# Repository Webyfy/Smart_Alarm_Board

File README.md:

View this project on [CADLAB.io](https://cadlab.io/project/27515). 

# Smart_Alarm_Board

## Description
Let people know what your project can do specifically. Provide context and add a link to any reference visitors might be unfamiliar with. A list of Features or a Background subsection can also be added here. If there are alternatives to your project, this is a good place to list differentiating factors.

## Badges
On some READMEs, you may see small images that convey metadata, such as whether or not all the tests are passing for the project. You can use Shields to add some to your README. Many services also have instructions for adding a badge.

## Visuals
Depending on what you are making, it can be a good idea to include screenshots or even a video (you'll frequently see GIFs rather than actual videos). Tools like ttygif can help, but check out Asciinema for a more sophisticated method.

## Installation
Within a particular ecosystem, there may be a common way of installing things, such as using Yarn, NuGet, or Homebrew. However, consider the possibility that whoever is reading your README is a novice and would like more guidance. Listing specific steps helps remove ambiguity and gets people to using your project as quickly as possible. If it only runs in a specific context like a particular programming language version or operating system or has dependencies that have to be installed manually, also add a Requirements subsection.

## Usage
Use examples liberally, and show the expected output if you can. It's helpful to have inline the smallest example of usage that you can demonstrate, while providing links to more sophisticated examples if they are too long to reasonably include in the README.

## Support
Tell people where they can go to for help. It can be any combination of an issue tracker, a chat room, an email address, etc.

## Roadmap
If you have ideas for releases in the future, it is a good idea to list them in the README.

## Contributing
State if you are open to contributions and what your requirements are for accepting them.

For people who want to make changes to your project, it's helpful to have some documentation on how to get started. Perhaps there is a script that they should run or some environment variables that they need to set. Make these steps explicit. These instructions could also be useful to your future self.

You can also document commands to lint the code or run tests. These steps help to ensure high code quality and reduce the likelihood that the changes inadvertently break something. Having instructions for running tests is especially helpful if it requires external setup, such as starting a Selenium server for testing in a browser.

## Authors and acknowledgment
Show your appreciation to those who have contributed to the project.

## License
For open source projects, say how it is licensed.

## Project status
If you have run out of energy or time for your project, put a note at the top of the README saying that development has slowed down or stopped completely. Someone may choose to fork your project or volunteer to step in as a maintainer or owner, allowing your project to keep going. You can also make an explicit request for maintainers.

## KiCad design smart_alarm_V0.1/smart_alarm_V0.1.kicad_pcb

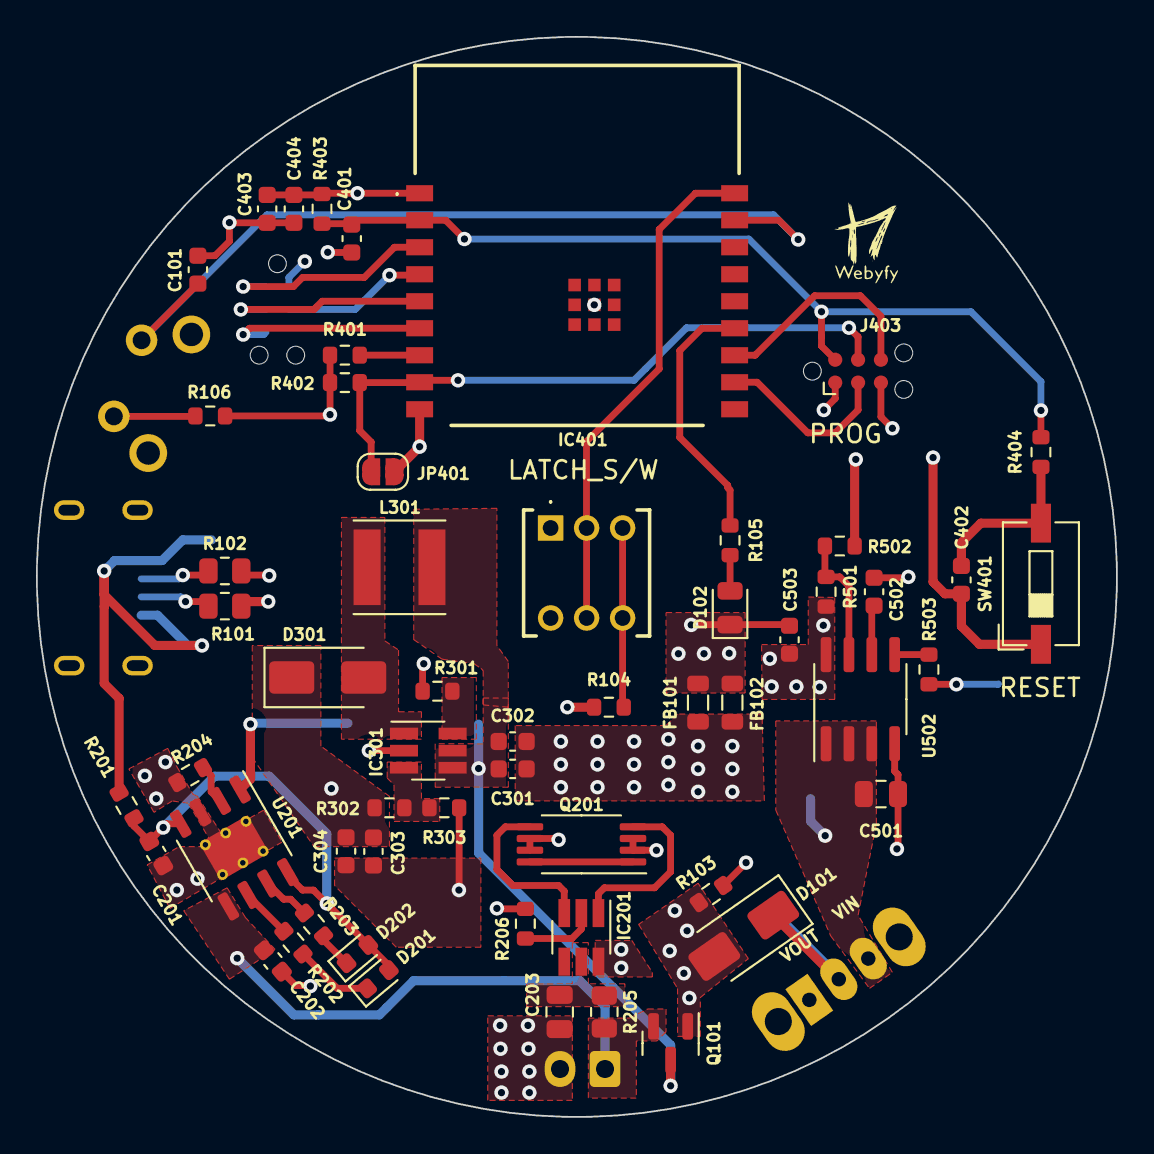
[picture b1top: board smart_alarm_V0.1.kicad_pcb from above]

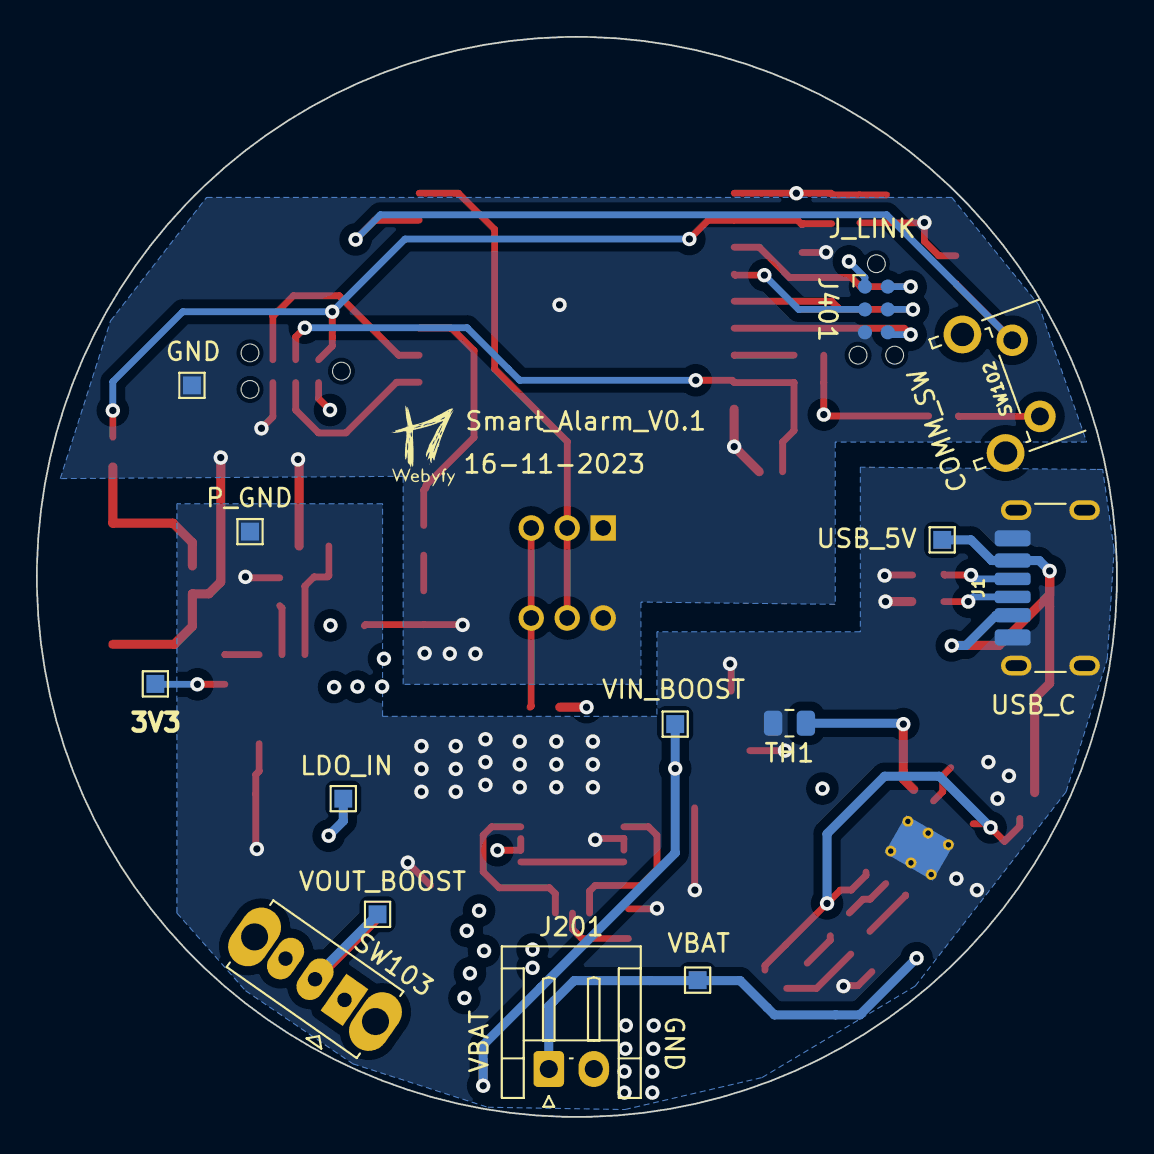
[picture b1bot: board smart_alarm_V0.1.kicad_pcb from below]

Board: 4 copper layers, 60.0 x 60.0 mm, 70 parts (14 on the bottom side), 45 nets.

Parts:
C101, C301, C304, C404, C502: 100nF; C_0603_1608Metric
C201, C202, C403: 10uF; C_0603_1608Metric
C203: 100nF; C_0805_2012Metric
C302, C303: 22uF; C_0603_1608Metric
C401, C402: C; C_0603_1608Metric
C501: 4.7uF; C_0805_2012Metric
C503: 1uF; C_0603_1608Metric
D101: B340; D_SMA
D102: LED; LED_0805_2012Metric
D201, D202: LED; LED_0603_1608Metric
D301: B340A; D_SMA
FB101, FB102: FerriteBead; L_0805_2012Metric
IC201: DW01+G; SOT-23-6_Handsoldering
IC301: FP6291; SOT-23-6_Handsoldering
IC401: ESP32-C3-WROOM-02-H4; ESP32C3WROOM02H4
J1: USB_C_Receptacle_PowerOnly_6P; USB_C_Receptacle_GCT_USB4125-xx-x-0190_6P_TopMnt_Horizontal
J201: LI-ION BATTARY; JST_EH_S2B-EH_1x02_P2.50mm_Horizontal
J401: JTAG; Tag-Connect_TC2030-IDC-NL_2x03_P1.27mm_Vertical
J403: PROG; Tag-Connect_TC2030-IDC-NL_2x03_P1.27mm_Vertical
JP401: Jumper_2_Open; SolderJumper-2_P1.3mm_Open_RoundedPad1.0x1.5mm
L301: 3.3uH; L_Taiyo-Yuden_MD-5050
Q101: DMG2301L; SOT-23
Q201: FS8205A; TSSOP-8_4.4x3mm_P0.65mm
R101, R102: 5.1K; R_0805_2012Metric
R103: 5.1K; R_0603_1608Metric
R104, R105, R106, R401, R402: 10k; R_0603_1608Metric
R201, R202, R203: 1K; R_0603_1608Metric
R204: 1.2K; R_0603_1608Metric
R205: 470E; R_0805_2012Metric
R206: 2K; R_0603_1608Metric
R301: 10K; R_0603_1608Metric
R302: 88K; R_0603_1608Metric
R303: 12K; R_0603_1608Metric
R403, R404: R; R_0603_1608Metric
R501: 113k; R_0603_1608Metric
R502: 15k; R_0603_1608Metric
R503: 100k; R_0603_1608Metric
SW101: Panic switch; XKB7070Z92
SW102: SW_Push; SW_Tactile_SPST_Angled_PTS645Vx58-2LFS
SW103: SW_SPDT; SW_Slide_1P2T_CK_OS102011MS2Q
SW401: SW_DIP_x01; SW_DIP_SPSTx01_Slide_6.7x4.1mm_W6.73mm_P2.54mm_LowProfile_J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
TH1: Thermistor_NTC; R_0805_2012Metric
TP1: OUT_BOOST; TestPoint_Pad_1.0x1.0mm
TP2: VBAT; TestPoint_Pad_1.0x1.0mm
TP3: 5V_BOOST; TestPoint_Pad_1.0x1.0mm
TP4: SW_OUT; TestPoint_Pad_1.0x1.0mm
TP5: 3V3; TestPoint_Pad_1.0x1.0mm
TP6: 5V; TestPoint_Pad_1.0x1.0mm
TP7: P_GND; TestPoint_Pad_1.0x1.0mm
TP8: GND; TestPoint_Pad_1.0x1.0mm
U201: TP4056; HSOP-8-1EP_3.9x4.9mm_P1.27mm_EP2.41x3.1mm_ThermalVias
U502: MCP1726-ADJxSN; SOIC-8_3.9x4.9mm_P1.27mm

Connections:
+3.3V: C403.2, C404.2, C503.1, IC401.1 (3V3), J401.1, J403.1, R104.1, R106.1, R401.1, R402.1, R403.2, R501.1, R503.1, TP5.1, U502.8 (Vout)
/5V: D101.2 (A), J1.A9 (VBUS), J1.B9 (VBUS), Q101.1 (G), R103.1, R201.1, TP6.1
/5V_BOOST/VIN: C301.1, C302.1, IC301.4 (EN), IC301.5 (VCC), L301.1, Q101.3 (D), TP3.1
/5V_BOOST/VOUT: C303.1, C304.1, D101.1 (K), D301.1 (K), R302.1, SW103.2 (B), TP1.1
/CC1: J1.A5 (CC1), R101.1
/CC2: J1.B5 (CC2), R102.1
/ESP32-C3-WROOM/EN: C401.2, IC401.2 (EN), J403.2, R403.1, R404.2
/ESP32-C3-WROOM/IO0: IC401.18 (IO0), SW101.2 (B), SW101.5 (B)
/ESP32-C3-WROOM/IO1: C101.1, IC401.17 (IO1), SW102.1
/ESP32-C3-WROOM/IO8: IC401.7 (IO8), R401.2
/ESP32-C3-WROOM/IO9: IC401.8 (IO9), J403.4, JP401.1 (A), R402.2
/ESP32-C3-WROOM/IO18: IC401.13 (IO18), R105.1
/ESP32-C3-WROOM/RXD: IC401.11 (RXD), J403.3
/ESP32-C3-WROOM/TCK: IC401.5 (IO6), J401.4
/ESP32-C3-WROOM/TDI: IC401.4 (IO5), J401.3
/ESP32-C3-WROOM/TDO: IC401.6 (IO7), J401.6
/ESP32-C3-WROOM/TMS: IC401.3 (IO4), J401.2
/ESP32-C3-WROOM/TXD: IC401.12 (TXD), J403.6
/LDO_3V3/VIN: C501.1, SW103.3 (C), TP4.1, U502.1 (Vin), U502.2 (Vin), U502.3 (~SHDN)
/TP4056/VBAT: C202.1, J201.1, Q101.2 (S), R205.2, TP2.1, U201.5 (BAT)
GND: C101.2, C401.1, C402.1, C403.1, C404.1, C503.2, D102.1 (K), FB101.2, FB102.2, IC401.9 (GND_1), IC401.19 (EPAD), J401.5, J403.5, JP401.2 (B), R502.2, SW101.1 (A), SW101.4 (A), SW401.1, TP8.1
GNDPWR: C201.2, C202.2, C301.2, C302.2, C303.2, C304.2, C501.2, C502.2, FB101.1, FB102.1, IC301.2 (GND), J1.A12 (GND), J1.B12 (GND), J1.S1 (SHIELD), Q201.6 (S2_1), Q201.7 (S2_2), R101.2, R102.2, R103.2, R204.2, R206.2, R301.2, R303.2, TH1.2, TP7.1, U201.3 (GND_3), U201.9 (EP), U502.4 (GND)
unnamed: C402.2, R404.1, SW401.2
unnamed: D102.2 (A), R105.2
unnamed: C201.1, D201.2 (A), D202.2 (A), R201.2, U201.4 (VCC4), U201.8 (CE)
unnamed: D201.1 (K), R202.1
unnamed: D202.1 (K), R203.1
unnamed: D301.2 (A), IC301.1 (LX), L301.2
unnamed: IC201.2 (CS), R206.1
unnamed: C203.2, IC201.6 (GND), J201.2, Q201.2 (S1_1), Q201.3 (S1_2)
unnamed: IC201.3 (OC), Q201.5 (G2)
unnamed: IC201.1 (OD), Q201.4 (G1)
unnamed: C203.1, IC201.5 (VCC), R205.1
unnamed: IC301.3 (FB), R302.2, R303.1
unnamed: IC301.6 (OC), R301.1
unnamed: Q201.1 (D12_1), Q201.8 (D12_2)
unnamed: R104.2, SW101.3 (C), SW101.6 (C)
unnamed: R106.2, SW102.2
unnamed: R204.1, U201.2 (PROG2)
unnamed: TH1.1, U201.1 (TEMP1)
unnamed: R203.2, U201.7 (~CHRG)
unnamed: R202.2, U201.6 (~STDBY)
unnamed: R501.2, R502.1, U502.7 (ADJ)
unnamed: C502.1, U502.6 (Cdelay)
unnamed: R503.2, U502.5 (PWRGD)

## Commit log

2023-11-14 Add smart_alarm_v0.1
2023-11-14 Add git ignore
2023-11-14 Intial change in Readme
2023-11-14 Backlink to CADLAB.io has been added.
2023-11-16 Verify footprint
2023-11-16 Remove backup folder
2023-11-20 Footprint rearrange
